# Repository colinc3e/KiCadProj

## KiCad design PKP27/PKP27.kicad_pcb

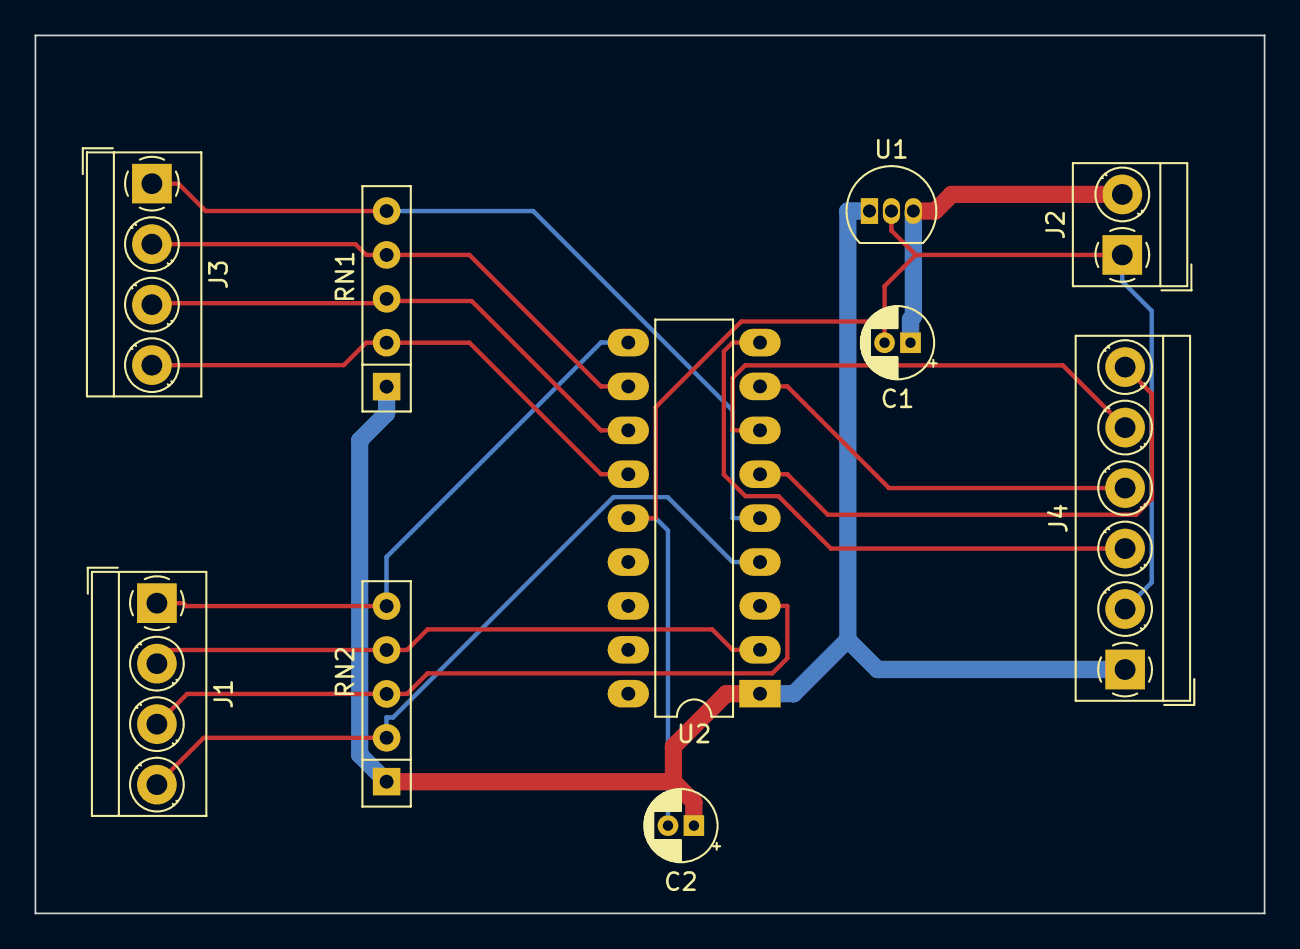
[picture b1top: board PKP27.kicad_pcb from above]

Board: 2 copper layers, 71.1 x 50.8 mm, 10 parts (0 on the bottom side), 15 nets.

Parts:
C1: 330pF; CP_Radial_D4.0mm_P1.50mm
C2: 100pF; CP_Radial_D4.0mm_P1.50mm
J1, J3: Screw_Terminal_01x04; TerminalBlock_MetzConnect_Type059_RT06304HBWC_1x04_P3.50mm_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
J2: Screw_Terminal_01x02; TerminalBlock_MetzConnect_Type059_RT06302HBWC_1x02_P3.50mm_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
J4: Screw_Terminal_01x06; TerminalBlock_MetzConnect_Type059_RT06306HBWC_1x06_P3.50mm_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
RN1, RN2: 10k; R_Array_SIP5
U1: L78L05_TO92; TO-92_Inline
U2: PIC16F684-IP; DIP-18_W7.62mm_LongPads

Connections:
+5V: C2.1, J4.1, RN1.1 (common), RN2.1 (common), U1.1 (VO), U2.1 (VDD)
+12V: C1.1, J2.2, U1.3 (VI)
/RC0: J1.1, RN2.5 (R4), U2.10 (C2IN+/AN4/RC0)
/RC1: J4.3, U2.9 (C2IN-/AN5/RC1)
/RC5: J3.1, RN1.5 (R4), U2.5 (P1A/CCP1/RC5)
GND: C1.2, C2.2, J2.1, J4.2, U1.2 (GND), U2.14 (VSS)
unnamed: J1.2, RN2.4 (R3), U2.2 (RA5/T1CKI/OSC1/CLKIN)
unnamed: J1.3, RN2.3 (R2), U2.3 (RA4/AN3/~T1G/OSC2/CLKOUT)
unnamed: J1.4, RN2.2 (R1), U2.4 (RA3/~MCLR/Vpp)
unnamed: J3.2, RN1.4 (R3), U2.11 (RA2/AN2/T0CKI/INT/C1OUT)
unnamed: J3.3, RN1.3 (R2), U2.12 (RA1/AN1/C1IN-/Vref/ICSPCLK)
unnamed: J3.4, RN1.2 (R1), U2.13 (RA0/AN0/C1IN+/ICSPDAT/ULPWU)
unnamed: J4.4, U2.8 (P1D/AN6/RC2)
unnamed: J4.5, U2.7 (P1C/AN7/RC3)
unnamed: J4.6, U2.6 (P1B/C2OUT/RC4)

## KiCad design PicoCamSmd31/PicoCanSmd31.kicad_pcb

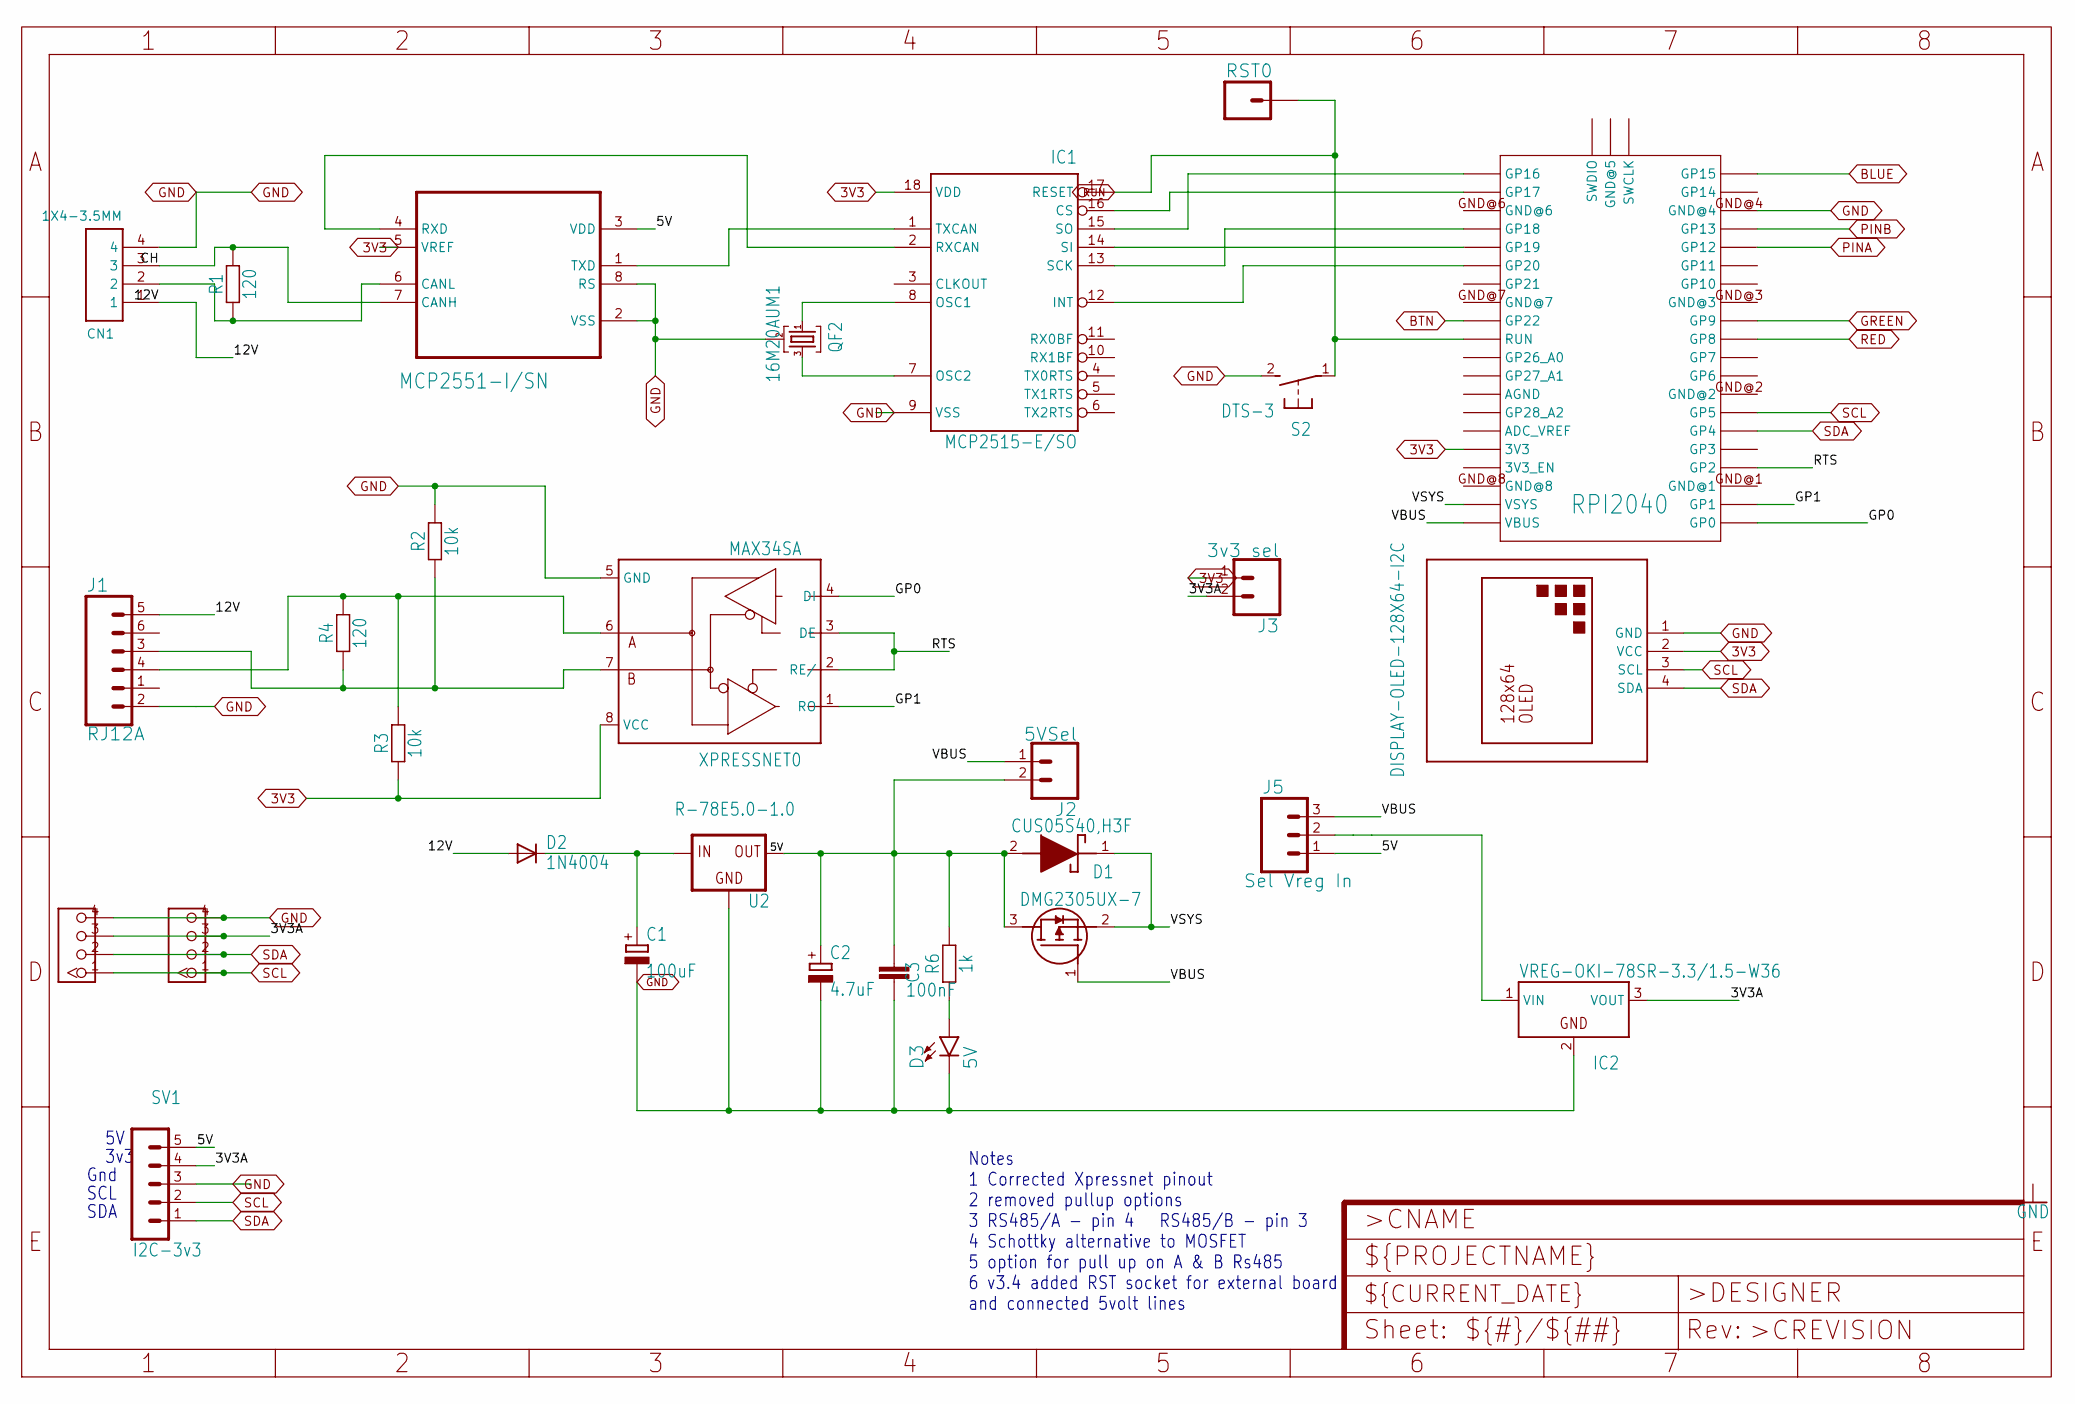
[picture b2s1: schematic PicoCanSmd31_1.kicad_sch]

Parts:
C1: 100uF; E5-8,5
C2: 4.7uF; E5-8,5
C3: 100nF; C025-024X044
CN1: 1X4-3.5MM; 1X04-3.5MM
D1: CUS05S40,H3F; 1SS357TPH3F
D2: 1N4004; DO41-10
D3: 5V; LED_3MM
IC1: MCP2515-E/SO; SO18L
IC2: VREG-OKI-78SR-3.3/1.5-W36; OKI-78SR
J1: RJ12A
J2: 5VSel; 1X02
J3: 3v3 sel; 1X02
J4, J6: 4P-2.0; HW4-2.0
J5: Sel Vreg In; 1X03
Q3: DMG2305UX-7; SOT96P240X110-3N
QF2: 16M20AUM1; UM1
R1, R4: 120; C1206
R2, R3: 10k; C1206
R6: 1k; C1206
RPI2040: RPI_PICO_IG-TH; RPI_PICO_TH
RST0: CONN_01; 1X01
S2: DTS-3
SV1: I2C-3v3; MA05-1
U2: R-78E5.0-1.0; DC-DC_CONVERTER_78XX
U$1: DISPLAY-OLED-128X64-I2C
U$3: MCP2551-I/SN; SOIC127P600X175-8N
XPRESSNET0: MAX34SA; SO08

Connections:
3V3: IC1.18 (VDD), J3.1, R3.1, RPI2040.3V3, U$1.2 (VCC), U$3.5 (VREF), XPRESSNET0.8 (VCC); also elsewhere on the board
3V3A: IC2.3 (VOUT), J3.2, J4.3, J6.3, SV1.4
5V: C2.+, C3.1, D1.2 (A), J2.2, J5.1, Q3.3 (D), R6.2, SV1.5, U2.VOUT (OUT), U$3.3 (VDD)
12V: CN1.1, D2.A, J1.5
BLUE: RPI2040.GP15; also elsewhere on the board
BTN: RPI2040.GP22; also elsewhere on the board
CH: CN1.3, R1.2, U$3.7 (CANH)
CL: CN1.2, R1.1, U$3.6 (CANL)
GND: C1.-, C2.-, C3.2, CN1.4, D3.K (C), IC1.9 (VSS), IC2.2 (GND), J1.2 (1), J4.4, J6.4, QF2.2, R2.2, RPI2040.GND@4, S2.2, SV1.3, U2.GND, U$1.1 (GND), U$3.2 (VSS), U$3.8 (RS), XPRESSNET0.5 (GND); also elsewhere on the board
GP0: RPI2040.GP0, XPRESSNET0.4 (DI)
GP1: RPI2040.GP1, XPRESSNET0.1 (RO)
GREEN: RPI2040.GP9; also elsewhere on the board
unnamed: J1.4 (3), R3.2, R4.2, XPRESSNET0.6 (A)
unnamed: J1.3 (4), R2.1, R4.1, XPRESSNET0.7 (B)
unnamed: IC1.1 (TXCAN), U$3.1 (TXD)
unnamed: IC1.2 (RXCAN), U$3.4 (RXD)
unnamed: IC1.8 (OSC1), QF2.1
unnamed: IC1.7 (OSC2), QF2.3
unnamed: IC1.16 (CS), RPI2040.GP17
unnamed: IC1.15 (SO), RPI2040.GP16
unnamed: IC1.14 (SI), RPI2040.GP19
unnamed: IC1.13 (SCK), RPI2040.GP18
unnamed: IC1.12 (INT), RPI2040.GP20
unnamed: IC2.1 (VIN), J5.2
unnamed: C1.+, D2.C, U2.VIN (IN)
unnamed: D3.A, R6.1
PINA: RPI2040.GP12; also elsewhere on the board
PINB: RPI2040.GP13; also elsewhere on the board
RED: RPI2040.GP8; also elsewhere on the board
RTS: RPI2040.GP2, XPRESSNET0.2 (RE/), XPRESSNET0.3 (DE)
RUN: IC1.17 (RESET), RPI2040.RUN, RST0.1, S2.1; also elsewhere on the board
SCL: J4.1, J6.1, RPI2040.GP5, SV1.2, U$1.3 (SCL); also elsewhere on the board
SDA: J4.2, J6.2, RPI2040.GP4, SV1.1, U$1.4 (SDA); also elsewhere on the board
VBUS: J2.1, J5.3, Q3.1 (G), RPI2040.VBUS
VSYS: D1.1 (K), Q3.2 (S), RPI2040.VSYS

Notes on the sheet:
Gnd
3v3
Notes 1 Corrected Xpressnet pinout 2 removed pullup options 3 RS485/A - pin 4 RS485/B - pin 3 4 Schottky alternative to MOSFET 5 option for pull up on A & B Rs485 6 v3.4 added RST socket for external board and connected 5volt lines
SDA
SCL

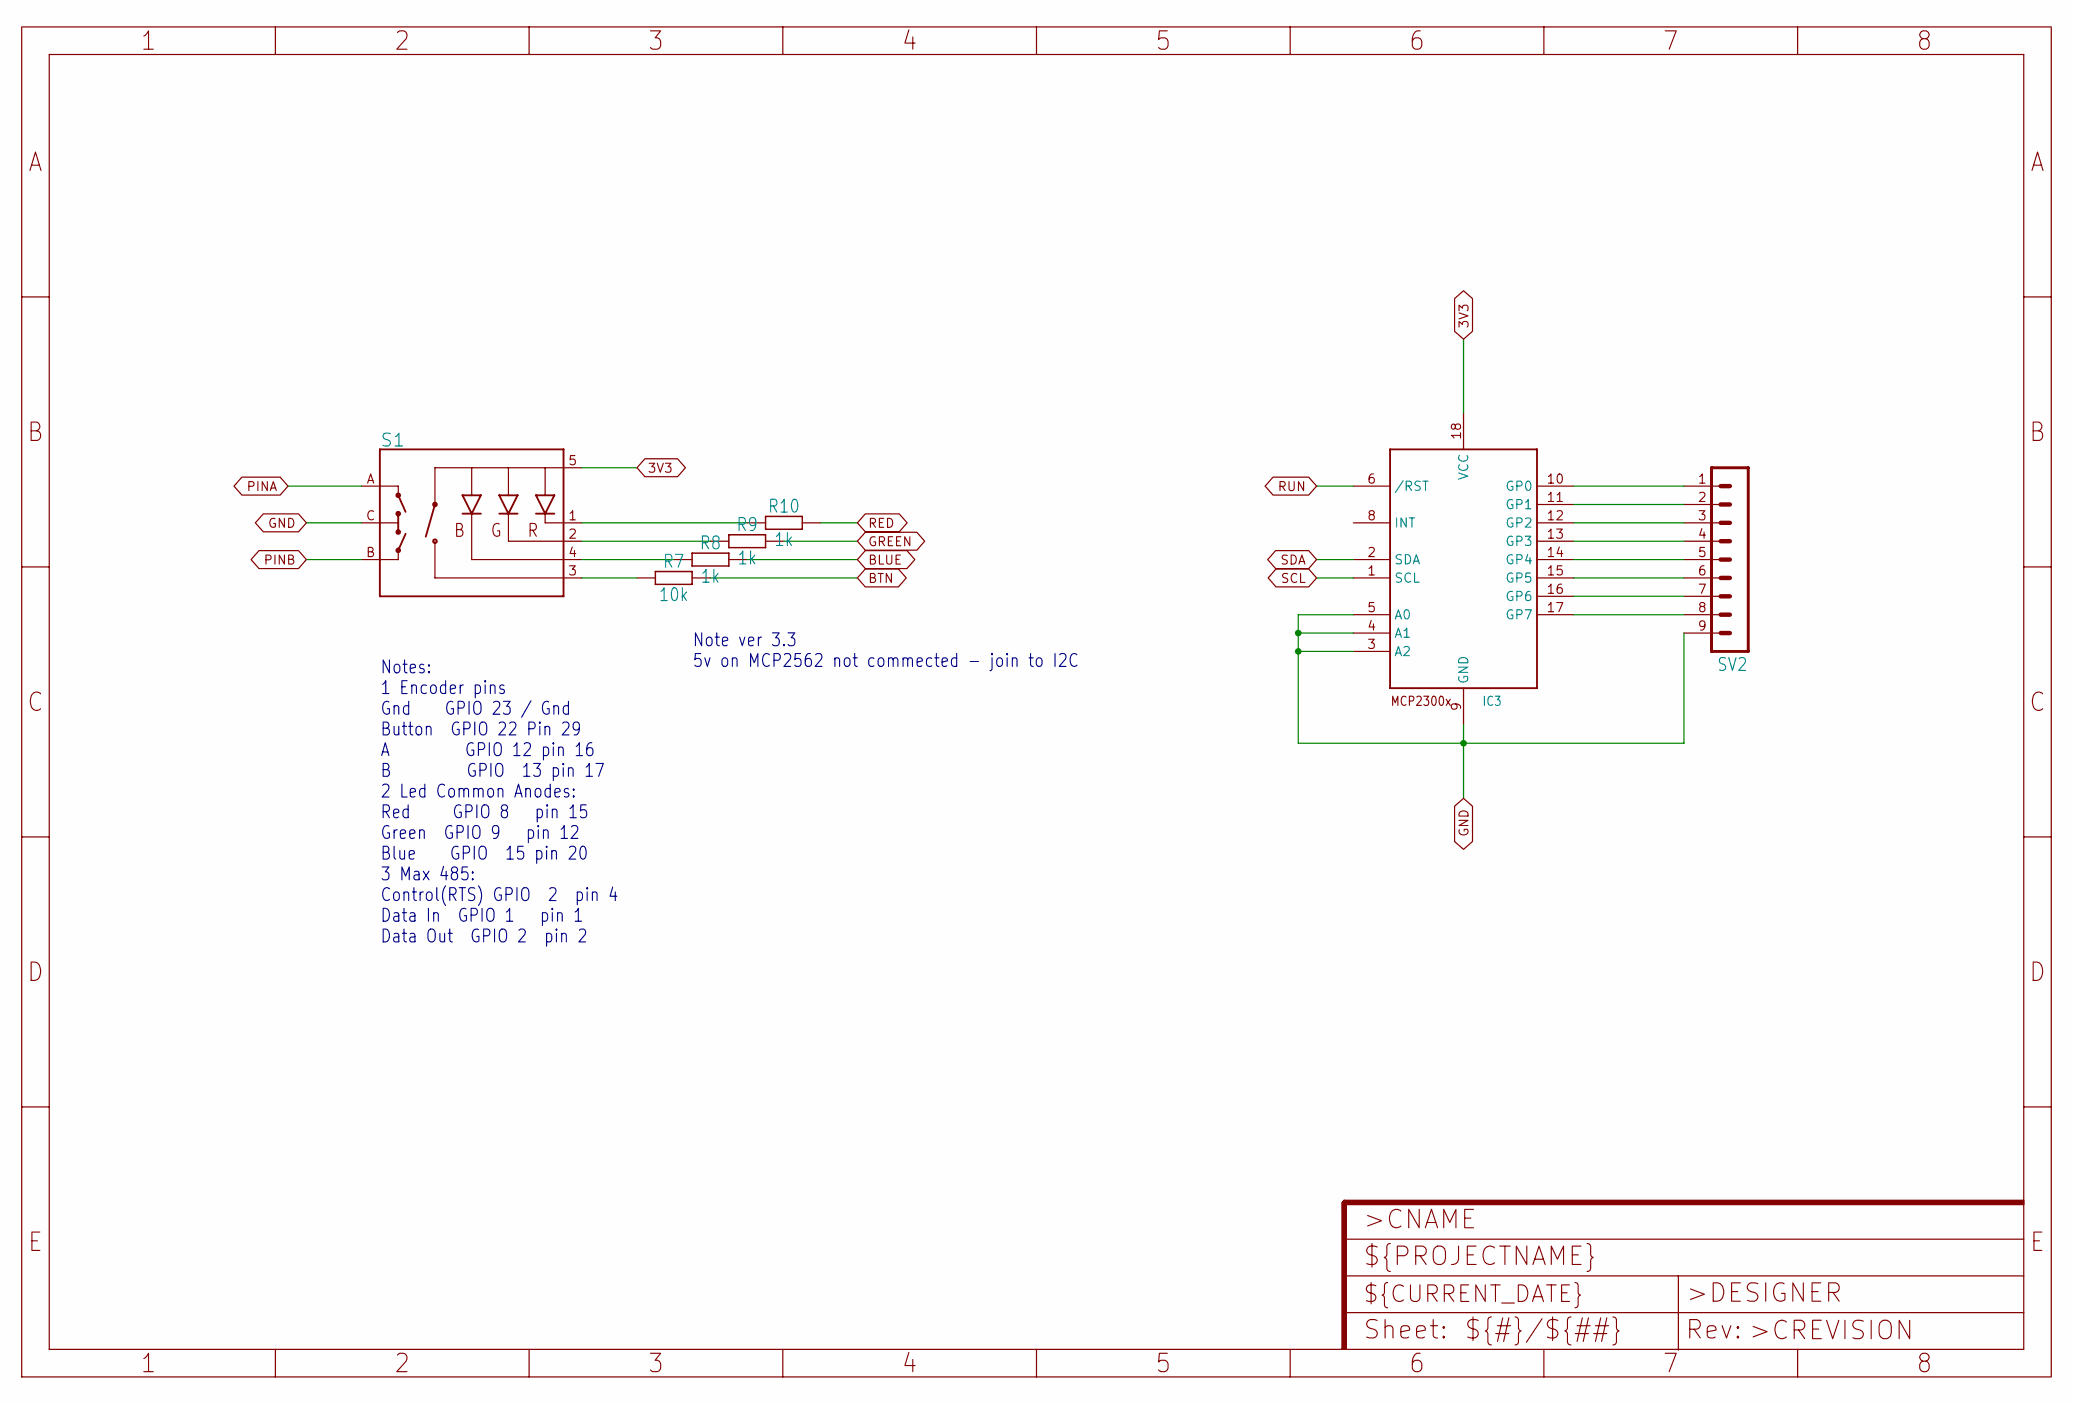
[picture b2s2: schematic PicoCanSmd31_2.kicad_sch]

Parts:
IC3: MCP23008/SO; SO18W
R7: 10k; C1206
R8, R9, R10: 1k; C1206
S1: ENCODER-RGB-SWITCH; ENCODER_LED_3
SV2: MA09-1

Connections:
3V3: IC3.18 (VCC), S1.5 (+); also elsewhere on the board
BLUE: R8.2; also elsewhere on the board
BTN: R7.2; also elsewhere on the board
GND: IC3.3 (A2), IC3.4 (A1), IC3.5 (A0), IC3.9 (GND), S1.C, SV2.9; also elsewhere on the board
GREEN: R9.2; also elsewhere on the board
unnamed: R8.1, S1.4 (-B)
unnamed: R9.1, S1.2 (-G)
unnamed: R10.1, S1.1 (-R)
unnamed: IC3.10 (GP0), SV2.1
unnamed: R7.1, S1.3 (SW)
unnamed: IC3.11 (GP1), SV2.2
unnamed: IC3.12 (GP2), SV2.3
unnamed: IC3.13 (GP3), SV2.4
unnamed: IC3.14 (GP4), SV2.5
unnamed: IC3.15 (GP5), SV2.6
unnamed: IC3.16 (GP6), SV2.7
unnamed: IC3.17 (GP7), SV2.8
PINA: S1.A; also elsewhere on the board
PINB: S1.B; also elsewhere on the board
RED: R10.2; also elsewhere on the board
RUN: IC3.6 (/RST); also elsewhere on the board
SCL: IC3.1 (SCL); also elsewhere on the board
SDA: IC3.2 (SDA); also elsewhere on the board

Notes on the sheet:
Notes: 1 Encoder pins Gnd GPIO 23 / Gnd Button GPIO 22 Pin 29 A GPIO 12 pin 16 B GPIO 13 pin 17 2 Led Common Anodes: Red GPIO 8 pin 15 Green GPIO 9 pin 12 Blue GPIO 15 pin 20 3 Max 485: Control(RTS) GPIO 2 pin 4 Data In GPIO 1 pin 1 Data Out GPIO 2 pin 2
Note ver 3.3 5v on MCP2562 not commected - join to I2C

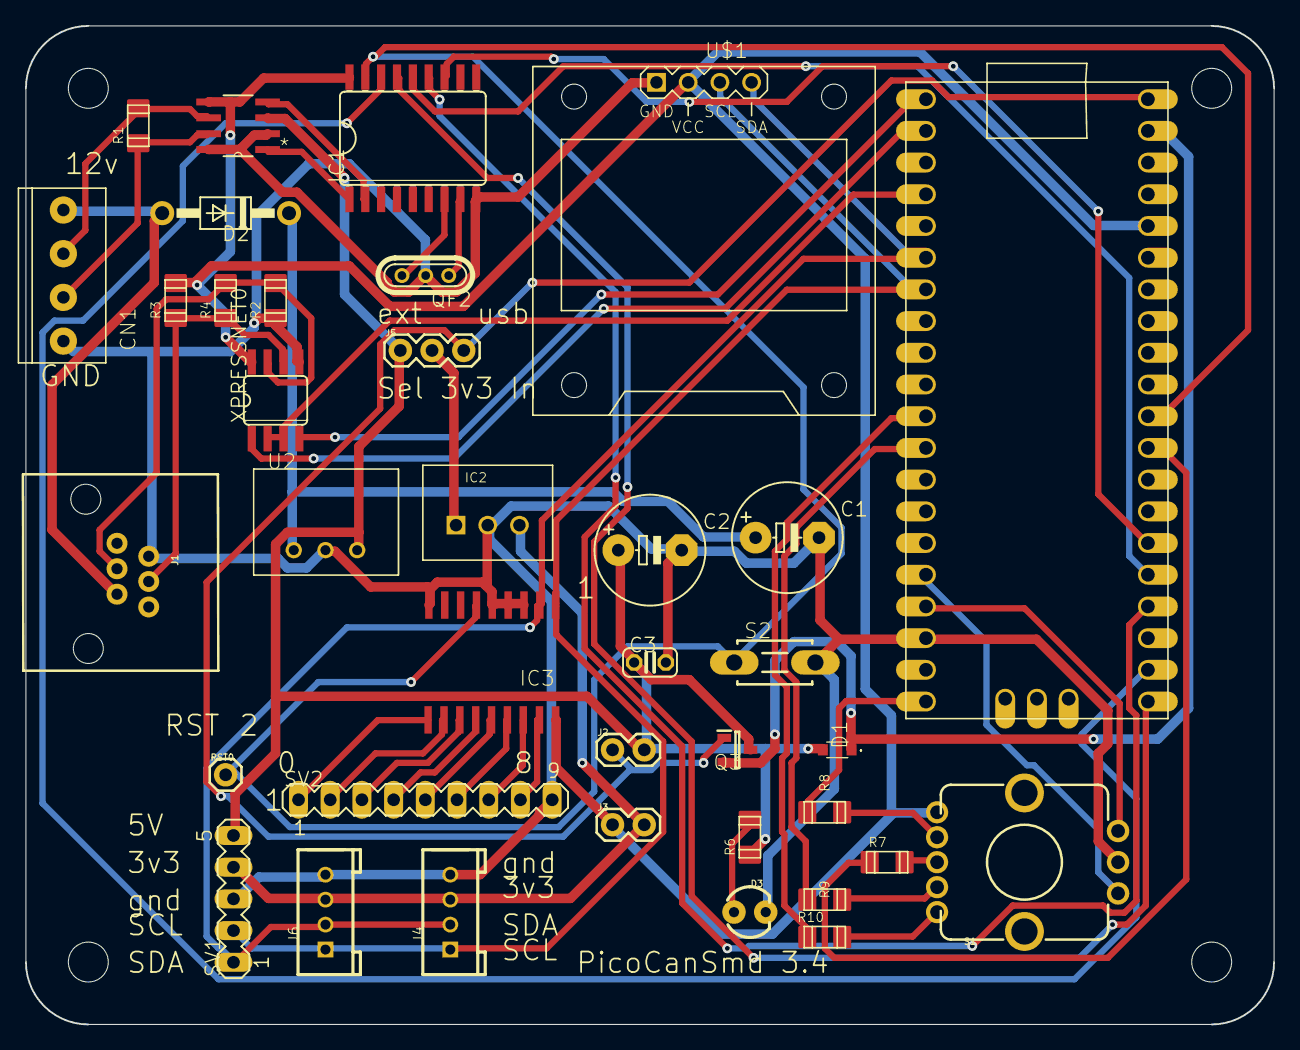
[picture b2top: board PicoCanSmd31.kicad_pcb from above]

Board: 2 copper layers, 100.0 x 80.0 mm, 41 parts (0 on the bottom side), 47 nets.

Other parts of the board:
@HOLE0, @HOLE1, @HOLE2, @HOLE3: (no value)

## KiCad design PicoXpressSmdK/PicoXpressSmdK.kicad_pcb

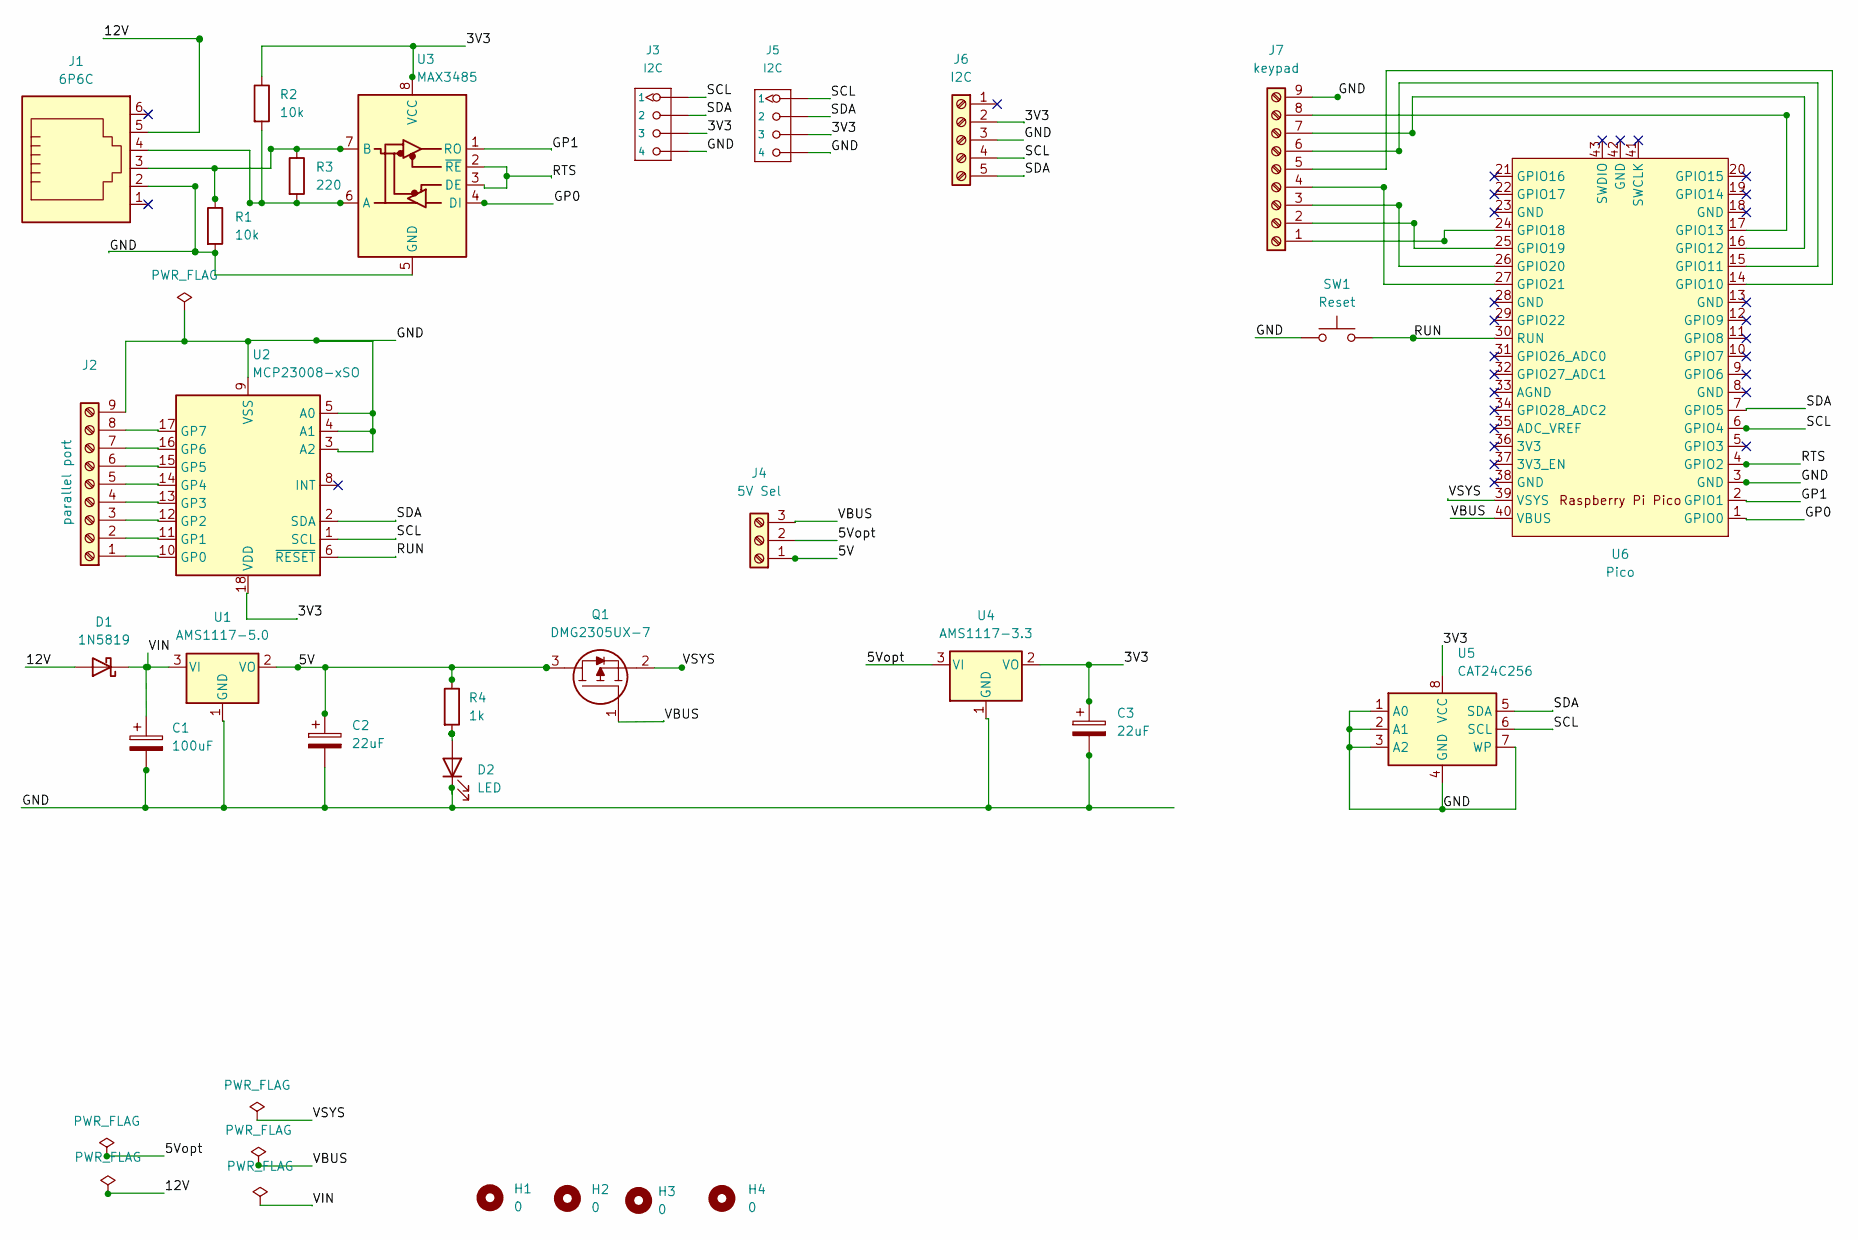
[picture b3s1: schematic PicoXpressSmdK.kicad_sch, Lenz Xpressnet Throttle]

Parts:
C1: 100uF; CP_Radial_Tantal_D8.0mm_P5.00mm
C2, C3: 22uF; CP_Radial_Tantal_D8.0mm_P5.00mm
D1: 1N5819; D_DO-41_SOD81_P10.16mm_Horizontal
D2: LED; LED_D3.0mm
H1, H2, H3, H4: 0; MountingHole_3.2mm_M3
J1: 6P6C; RJ12_Jaycar
J2: parallel port; PinHeader_1x09_P2.54mm_Vertical
J3, J5: I2C; HW4-2.0
J4: 5V Sel; PinHeader_1x03_P2.54mm_Vertical
J6: I2C; PinHeader_1x05_P2.54mm_Vertical
J7: keypad; PinHeader_1x09_P2.54mm_Vertical
Q1: DMG2305UX-7; SOT-23-3; Mouser Part Number 621-DMG2305UX-7
R1, R2: 10k; R_1206_3216Metric
R3: 220; R_1206_3216Metric
R4: 1k; R_1206_3216Metric
SW1: Reset; SW_Tactile_SPST_NO_Straight_CK_PTS636Sx25SMTRLFS
U1: AMS1117-5.0; SOT-223-3_TabPin2
U2: MCP23008-xSO; SOIC-18W_7.5x11.6mm_P1.27mm
U3: MAX3485; SOIC-8_3.9x4.9mm_P1.27mm
U4: AMS1117-3.3; SOT-223-3_TabPin2
U5: CAT24C256; DIP-8_W7.62mm_LongPads
U6: Pico; RP2040Pico

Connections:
/3V3: C3.1, J3.3, J5.3, J6.2, R2.1, U2.18 (VDD), U3.8 (VCC), U4.2 (VO), U5.8 (VCC)
/5V: C2.1, J4.1, Q1.3, R4.1, U1.2 (VO)
/5Vopt: J4.2, U4.3 (VI)
/12V: D1.2 (A), J1.5
/GND: C1.2, C2.2, C3.2, D2.1 (K), J1.2, J2.9, J3.4, J5.4, J6.3, J7.9, R1.2, SW1.1, U1.1 (GND), U2.3 (A2), U2.4 (A1), U2.5 (A0), U2.9 (VSS), U3.5 (GND), U4.1 (GND), U5.1 (A0), U5.2 (A1), U5.3 (A2), U5.4 (GND), U5.7 (WP), U6.3 (GND)
/GP0: U3.4 (DI), U6.1 (GPIO0)
/GP1: U3.1 (RO), U6.2 (GPIO1)
/RTS: U3.2 (~RE), U3.3 (DE), U6.4 (GPIO2)
/RUN: SW1.2, U2.6 (~RESET), U6.30 (RUN)
/SCL: J3.1, J5.1, J6.4, U2.1 (SCL), U5.6 (SCL), U6.6 (GPIO4)
/SDA: J3.2, J5.2, J6.5, U2.2 (SDA), U5.5 (SDA), U6.7 (GPIO5)
/VBUS: J4.3, Q1.1, U6.40 (VBUS)
/VIN: C1.1, D1.1 (K), U1.3 (VI)
/VSYS: Q1.2, U6.39 (VSYS)
unnamed: D2.2 (A), R4.2
unnamed: J1.3, R1.1, R3.1, U3.7 (B)
unnamed: J1.4, R2.2, R3.2, U3.6 (A)
unnamed: J2.1, U2.10 (GP0)
unnamed: J2.2, U2.11 (GP1)
unnamed: J2.3, U2.12 (GP2)
unnamed: J2.4, U2.13 (GP3)
unnamed: J2.5, U2.14 (GP4)
unnamed: J2.6, U2.15 (GP5)
unnamed: J2.7, U2.16 (GP6)
unnamed: J2.8, U2.17 (GP7)
unnamed: J7.1, U6.24 (GPIO18)
unnamed: J7.2, U6.25 (GPIO19)
unnamed: J7.3, U6.26 (GPIO20)
unnamed: J7.4, U6.27 (GPIO21)
unnamed: J7.5, U6.14 (GPIO10)
unnamed: J7.6, U6.15 (GPIO11)
unnamed: J7.7, U6.16 (GPIO12)
unnamed: J7.8, U6.17 (GPIO13)

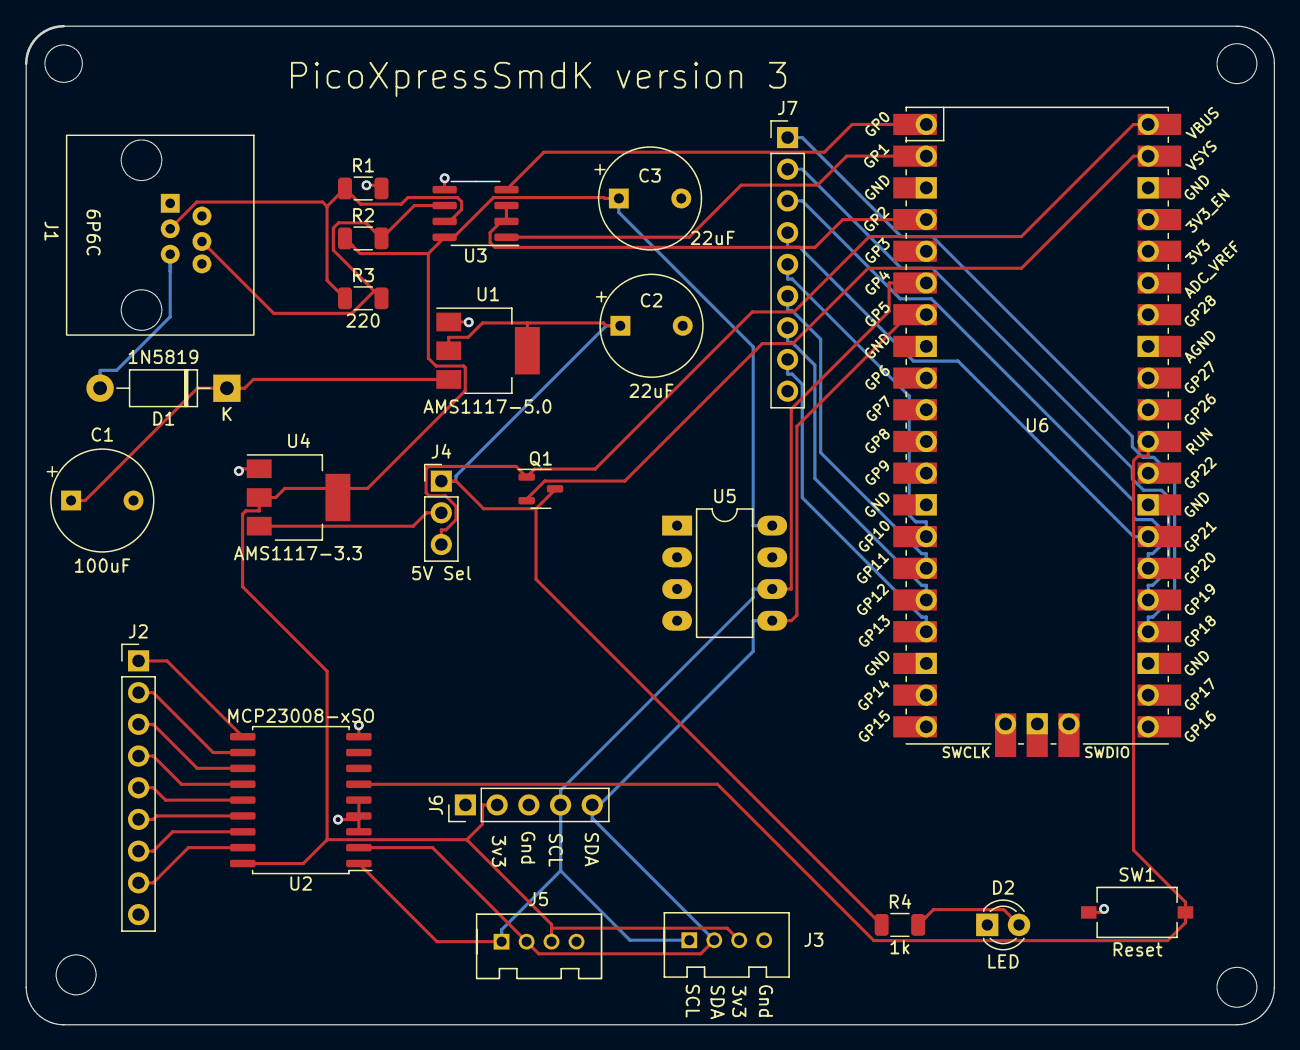
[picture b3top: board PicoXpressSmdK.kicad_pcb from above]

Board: 2 copper layers, 100.0 x 80.0 mm, 28 parts (0 on the bottom side), 33 nets.

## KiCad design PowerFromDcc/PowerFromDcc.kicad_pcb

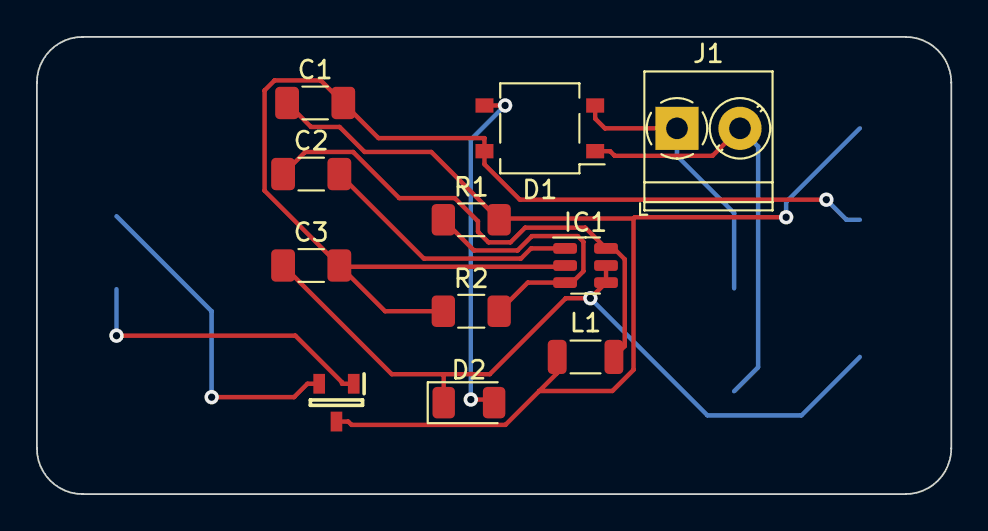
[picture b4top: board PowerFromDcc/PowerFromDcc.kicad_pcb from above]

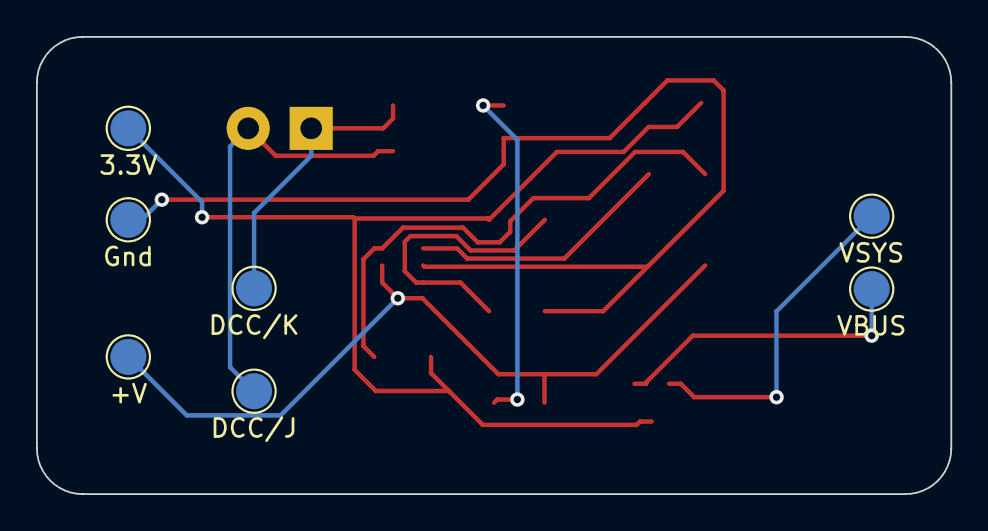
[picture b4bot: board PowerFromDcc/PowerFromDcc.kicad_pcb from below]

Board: 2 copper layers, 50.8 x 25.4 mm, 18 parts (7 on the bottom side), 11 nets.

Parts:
C1: 10u; C_1206_3216Metric_Pad1.33x1.80mm_HandSolder
C2: 100n; C_1206_3216Metric_Pad1.33x1.80mm_HandSolder
C3: 2.2uF/25V; C_1206_3216Metric_Pad1.33x1.80mm_HandSolder
D1: KMB24F; TO-269AA
D2: CUHS20F30; D_1206_3216Metric
IC1: AP64060QWU-7; TSOT-23-6
J1: DCC; TerminalBlock_Phoenix_PT-1,5-2-3.5-H_1x02_P3.50mm_Horizontal
J3: 3.3V; TestPoint_Pad_D2.0mm
J5: DCC/K; TestPoint_Pad_D2.0mm
J6: DCC/J; TestPoint_Pad_D2.0mm
L1: 10uH; L_1206_3216Metric
Q1: DMG2305UX-7; SOT96P240X110-3N
R1: 69k8; R_1206_3216Metric_Pad1.30x1.75mm_HandSolder
R2: 22k1; R_1206_3216Metric_Pad1.30x1.75mm_HandSolder
TP1: VSYS; TestPoint_Pad_D2.0mm
TP2: VBUS; TestPoint_Pad_D2.0mm
j2: Gnd; TestPoint_Pad_D2.0mm
j4: +V; TestPoint_Pad_D2.0mm

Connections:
+V: C3.1, D2.1 (K), IC1.4 (EN), IC1.5 (VIN), j4.1
/3.3V: C1.1, J3.1, L1.1, Q1.3, R1.2
/VP: D1.3 (+), D2.2 (A)
GND: C1.2, C3.2, D1.4 (-), IC1.2 (GND), R2.1, j2.1
unnamed: C2.2, IC1.1 (BST)
unnamed: IC1.3 (FB), R1.1, R2.2
unnamed: C2.1, IC1.6 (SW), L1.2
unnamed: D1.2, J1.1, J5.1
unnamed: D1.1, J1.2, J6.1
unnamed: Q1.1, TP2.1
unnamed: Q1.2, TP1.1

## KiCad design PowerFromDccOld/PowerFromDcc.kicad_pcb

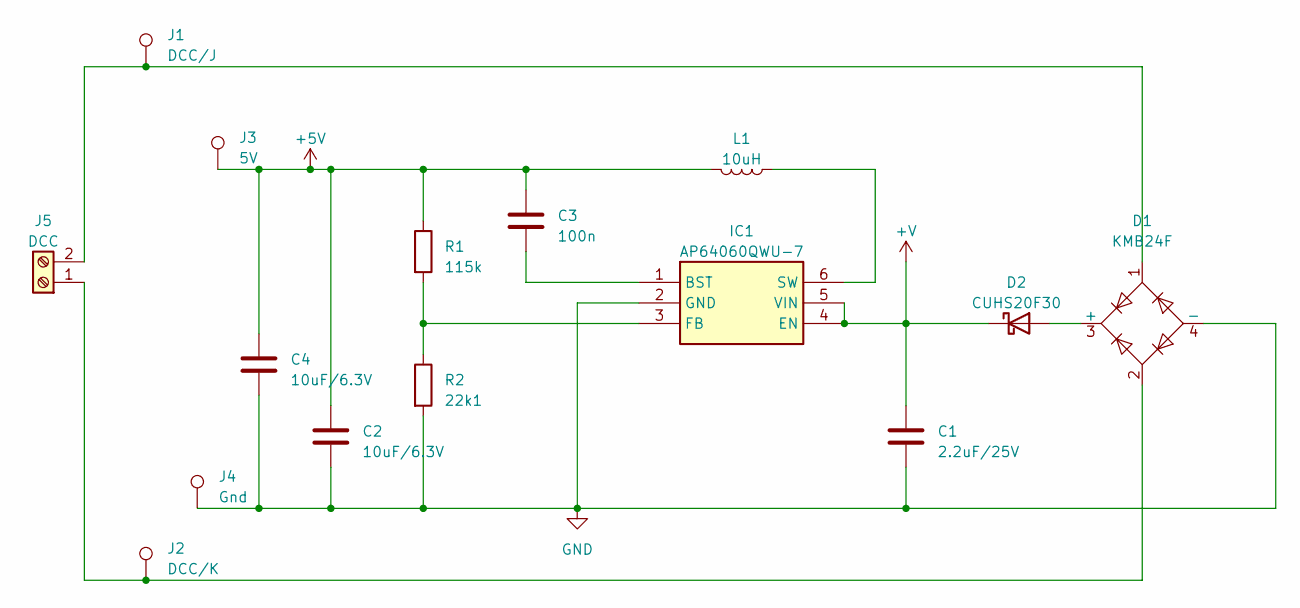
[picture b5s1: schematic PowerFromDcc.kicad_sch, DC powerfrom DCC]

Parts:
C1: 2.2uF/25V; C_1206_3216Metric
C2, C4: 10uF/6.3V; C_1206_3216Metric
C3: 100n; C_1206_3216Metric
D1: KMB24F; TO-269AA
D2: CUHS20F30; D_1206_3216Metric
IC1: AP64060QWU-7; SOT-23-6; Mouser Part Number 621-AP64060QWU-7
J1: DCC/J; TestPoint_Pad_D2.0mm
J2: DCC/K; TestPoint_Pad_D2.0mm
J3: 5V; TestPoint_Pad_D2.0mm
J4: Gnd; TestPoint_Pad_D2.0mm
J5: DCC; TerminalBlock_Phoenix_PT-1,5-2-3.5-H_1x02_P3.50mm_Horizontal
L1: 10uH; L_Wurth_WE-LQSH-2010
R1: 115k; R_1206_3216Metric
R2: 22k1; R_1206_3216Metric

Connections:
+5V: C2.1, C3.1, C4.1, J3.1, L1.2, R1.1
+V: C1.1, D2.1 (K), IC1.4 (EN), IC1.5 (VIN); also elsewhere on the board
GND: C1.2, C2.2, C4.2, D1.4 (-), IC1.2 (GND), J4.1, R2.2
unnamed 3: D1.3 (+), D2.2 (A); also elsewhere on the board
unnamed: C3.2, IC1.1 (BST)
unnamed: IC1.3 (FB), R1.2, R2.1
unnamed: IC1.6 (SW), L1.1
unnamed: D1.2, J2.1, J5.1
unnamed: D1.1, J1.1, J5.2

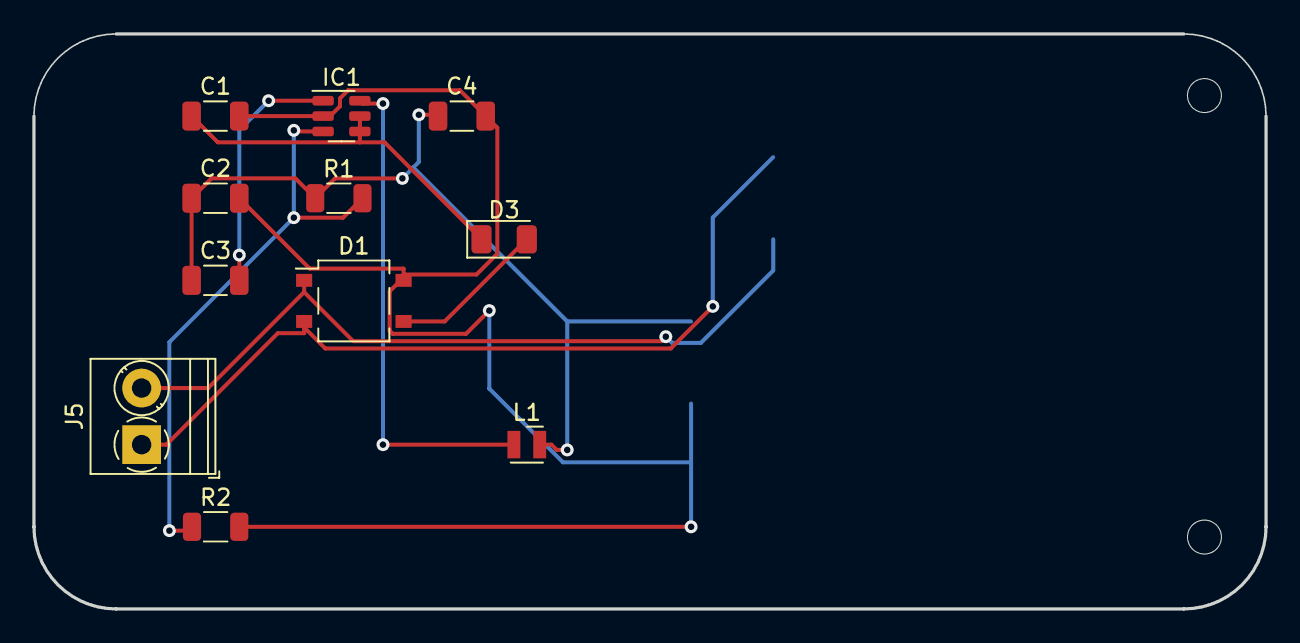
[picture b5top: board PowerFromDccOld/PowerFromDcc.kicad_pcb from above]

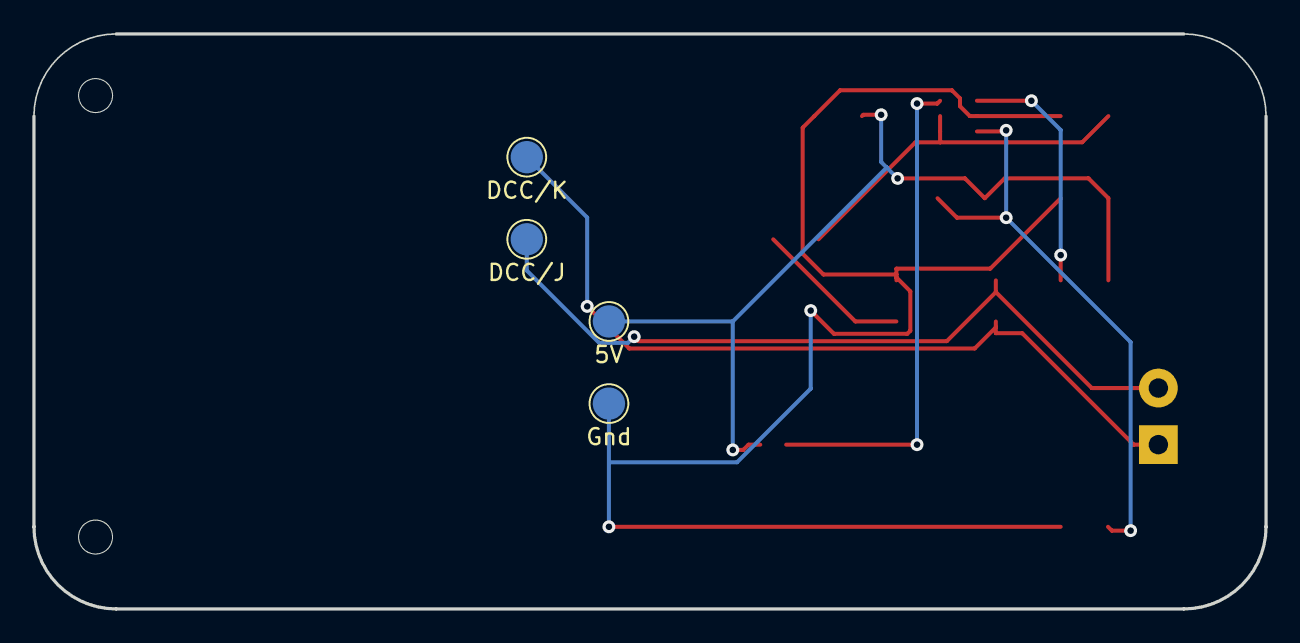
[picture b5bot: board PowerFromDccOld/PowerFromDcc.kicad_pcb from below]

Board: 2 copper layers, 76.2 x 35.6 mm, 17 parts (4 on the bottom side), 9 nets.

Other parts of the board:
D3: CUHS20F30; D_1206_3216Metric
a: MountingHole_2.1mm
b: MountingHole_2.1mm

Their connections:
+V: D3.1 (K); also elsewhere on the board
unnamed 3: D3.2 (A); also elsewhere on the board
